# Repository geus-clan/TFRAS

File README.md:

# TFRAS
PCB prototype for sensor board used with resistive automatic ablation sensor.

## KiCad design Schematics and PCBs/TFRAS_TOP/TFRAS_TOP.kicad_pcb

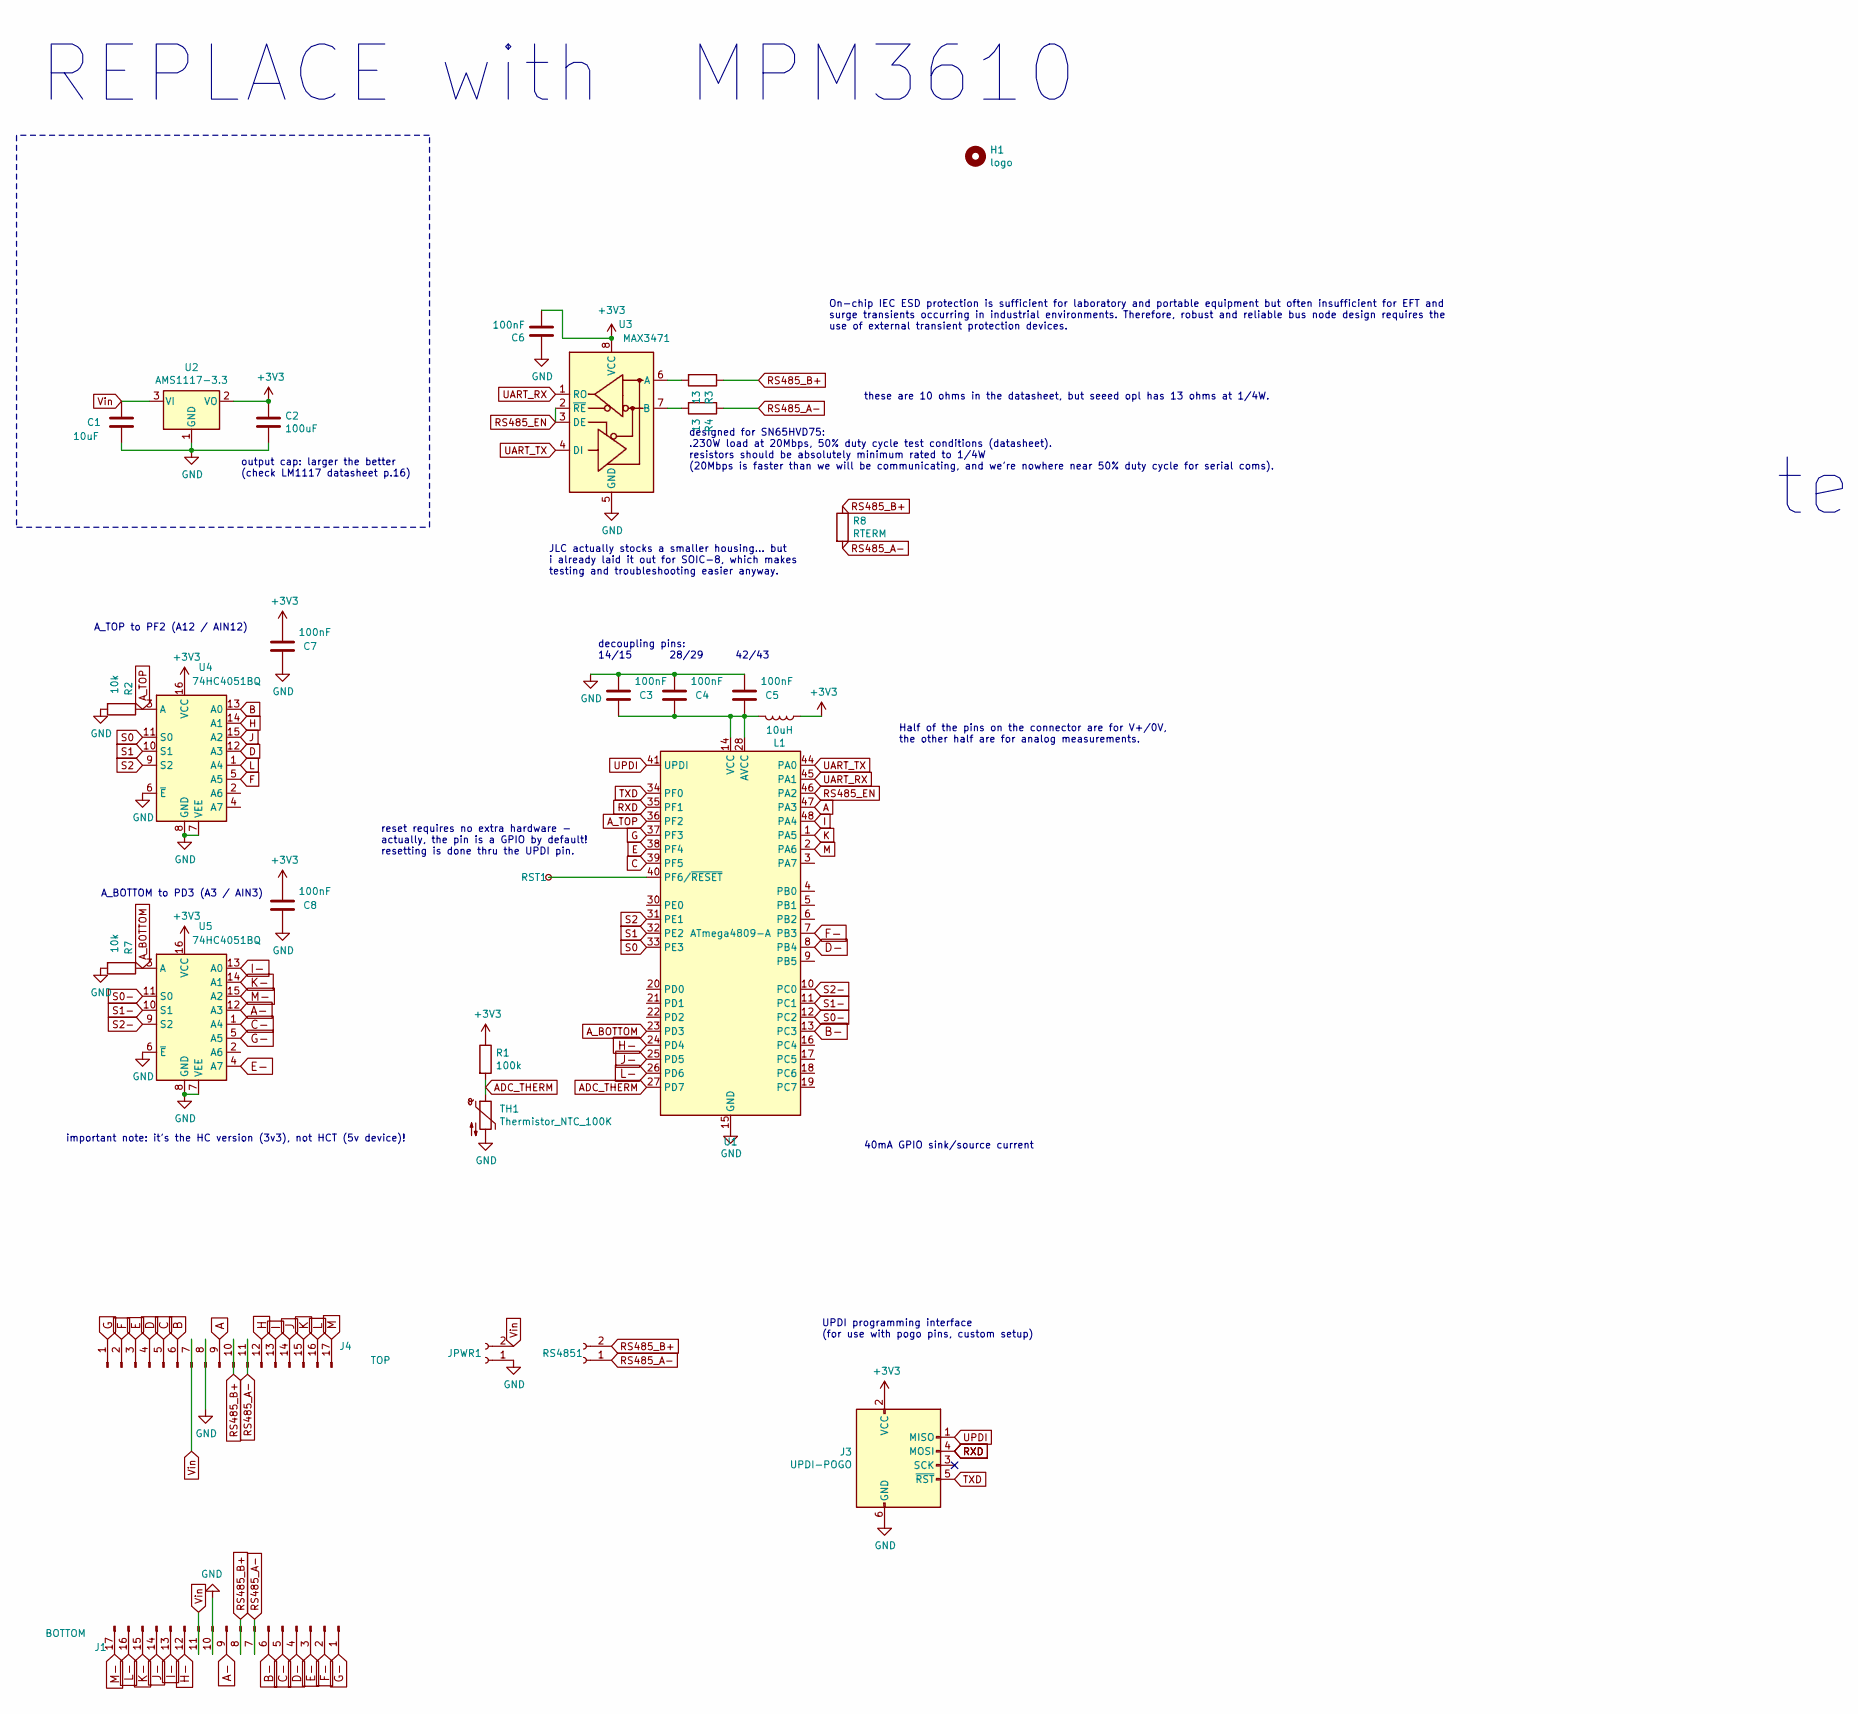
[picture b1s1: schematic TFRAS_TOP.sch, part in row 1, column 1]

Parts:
C1: 10uF; C_1206_3216Metric
C2: 100uF; C_1206_3216Metric
C3, C4, C5, C6, C7, C8: 100nF; C_0402_1005Metric; JLC part number C1525
H1: logo; TFRAS
J1: BOTTOM; Molex_200528-0170_1x17-1MP_P1.00mm_Horizontal
J3: UPDI-POGO; Tag-Connect_TC2030-IDC-NL_2x03_P1.27mm_Vertical; JLC part number ---
J4: TOP; Molex_200528-0170_1x17-1MP_P1.00mm_Horizontal; Mouser part number 538-200528-0170
JPWR1: Conn_01x02_Female; PinHeader_1x02_P1.27mm_Vertical; JLC part number ---
L1: 10uH; L_0603_1608Metric; JLC part number C1035
R1: 100k; R_0402_1005Metric
R2, R7: 10k; R_0805_2012Metric
R3, R4: 13; R_1206_3216Metric; JLC part number C17903
R8: RTERM; R_0805_2012Metric_Pad1.20x1.40mm_HandSolder; JLC part number ---
RS4851: Conn_01x02_Female; PinHeader_1x02_P1.27mm_Vertical; JLC part number ---
RST1: TestPoint_Small; TestPoint_Pad_1.0x1.0mm; JLC part number ---
TH1: Thermistor_NTC_100K; R_0603_1608Metric
U1: ATmega4809-A; TQFP-48_7x7mm_P0.5mm; JLC part number C189475
U2: AMS1117-3.3; SOT-223-3_TabPin2; JLC part number C6186
U3: MAX3471; MSOP-8_3x3mm_P0.65mm
U4, U5: 74HC4051BQ; SOT763-1(DHVQFN16); JLC part number C547696

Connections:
+3V3: C2.1, C6.2, C7.2, C8.2, J3.2 (VCC), L1.1, R1.1, U2.2 (VO), U3.8 (VCC), U4.16 (VCC), U5.16 (VCC)
A: J4.9, U1.47 (PA3)
A-: J1.9, U5.12 (A3)
ADC_THERM: R1.2, TH1.1, U1.27 (PD7)
A_BOTTOM: R7.1, U1.23 (PD3), U5.3 (A)
A_TOP: R2.1, U1.36 (PF2), U4.3 (A)
B: J4.6, U4.13 (A0)
B-: J1.6, U1.13 (PC3)
C: J4.5, U1.39 (PF5)
C-: J1.5, U5.1 (A4)
D: J4.4, U4.12 (A3)
D-: J1.4, U1.8 (PB4)
E: J4.3, U1.38 (PF4)
E-: J1.3, U5.4 (A7)
F: J4.2, U4.5 (A5)
F-: J1.2, U1.7 (PB3)
G: J4.1, U1.37 (PF3)
G-: J1.1, U5.5 (A5)
GND: C1.2, C2.2, C3.2, C4.2, C5.2, C6.1, C7.1, C8.1, J1.10, J3.6 (GND), J4.8, JPWR1.1, R2.2, R7.2, TH1.2, U1.15 (GND), U1.29 (GND), U1.43 (GND), U2.1 (GND), U3.5 (GND), U4.6 (~E), U4.7 (VEE), U4.8 (GND), U5.6 (~E), U5.7 (VEE), U5.8 (GND)
H: J4.12, U4.14 (A1)
H-: J1.12, U1.24 (PD4)
I: J4.13, U1.48 (PA4)
I-: J1.13, U5.13 (A0)
J: J4.14, U4.15 (A2)
J-: J1.14, U1.25 (PD5)
K: J4.15, U1.1 (PA5)
K-: J1.15, U5.14 (A1)
L: J4.16, U4.1 (A4)
L-: J1.16, U1.26 (PD6)
M: J4.17, U1.2 (PA6)
M-: J1.17, U5.15 (A2)
unnamed: C3.1, C4.1, C5.1, L1.2, U1.14 (VCC), U1.28 (AVCC), U1.42 (VCC)
unnamed: R3.2, U3.6 (A)
unnamed: R4.2, U3.7 (B)
unnamed: RST1.1, U1.40 (PF6/~RESET)
RS485_A-: J1.7, J4.11, R4.1, R8.2, RS4851.1
RS485_B+: J1.8, J4.10, R3.1, R8.1, RS4851.2
RS485_EN: U1.46 (PA2), U3.2 (~RE), U3.3 (DE)
RXD: J3.4 (MOSI), U1.35 (PF1)
S0: U1.33 (PE3), U4.11 (S0)
S0-: U1.12 (PC2), U5.11 (S0)
S1: U1.32 (PE2), U4.10 (S1)
S1-: U1.11 (PC1), U5.10 (S1)
S2: U1.31 (PE1), U4.9 (S2)
S2-: U1.10 (PC0), U5.9 (S2)
TXD: J3.5 (~RST), U1.34 (PF0)
UART_RX: U1.45 (PA1), U3.1 (RO)
UART_TX: U1.44 (PA0), U3.4 (DI)
UPDI: J3.1 (MISO), U1.41 (UPDI)
Vin: C1.1, J1.11, J4.7, JPWR1.2, U2.3 (VI)

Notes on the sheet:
test RS485 section
test points from serial port (uart)
40mA GPIO sink/source current
decoupling pins: 14/15 28/29 42/43
UPDI programming interface (for use with pogo pins, custom setup)
A_TOP to PF2 (A12 / AIN12)
A_BOTTOM to PD3 (A3 / AIN3)
Half of the pins on the connector are for V+/0V, the other half are for analog measurements.
On-chip IEC ESD protection is sufficient for laboratory and portable equipment but often insufficient for EFT and surge transients occurring in industrial environments. Therefore, robust and reliable bus node design requires the use of external transient protection devices.
output cap: larger the better (check LM1117 datasheet p.16)
designed for SN65HVD75: .230W load at 20Mbps, 50% duty cycle test conditions (datasheet). resistors should be absolutely minimum rated to 1/4W (20Mbps is faster than we will be communicating, and we’re nowhere near 50% duty cycle for serial coms).
JLC actually stocks a smaller housing… but i already laid it out for SOIC-8, which makes testing and troubleshooting easier anyway.
these are 10 ohms in the datasheet, but seeed opl has 13 ohms at 1/4W.
reset requires no extra hardware - actually, the pin is a GPIO by default! resetting is done thru the UPDI pin.
important note: it’s the HC version (3v3), not HCT (5v device)!
REPLACE with MPM3610

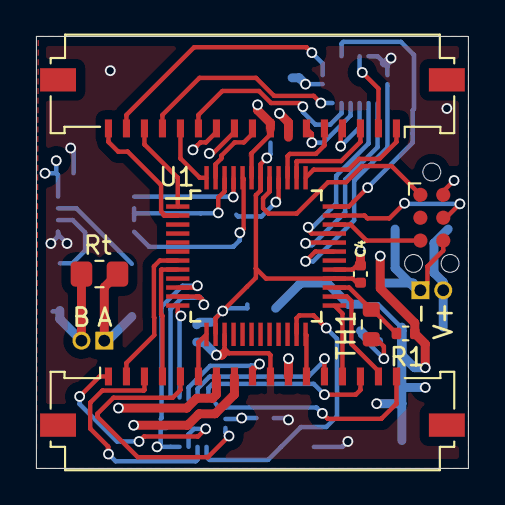
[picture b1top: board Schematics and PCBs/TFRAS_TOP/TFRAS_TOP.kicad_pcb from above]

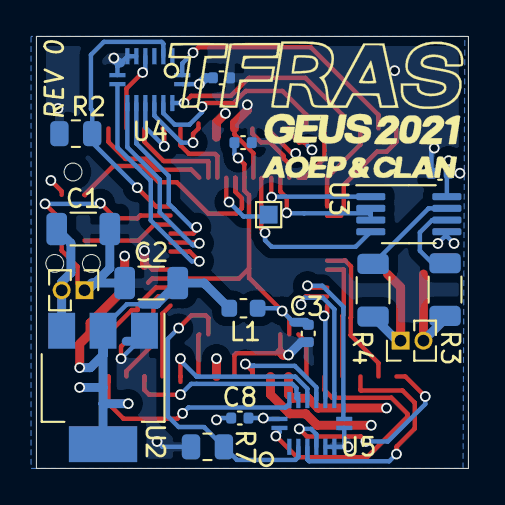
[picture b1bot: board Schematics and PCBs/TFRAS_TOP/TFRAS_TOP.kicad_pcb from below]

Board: 4 copper layers, 24.0 x 24.0 mm, 28 parts (20 on the bottom side), 50 nets.

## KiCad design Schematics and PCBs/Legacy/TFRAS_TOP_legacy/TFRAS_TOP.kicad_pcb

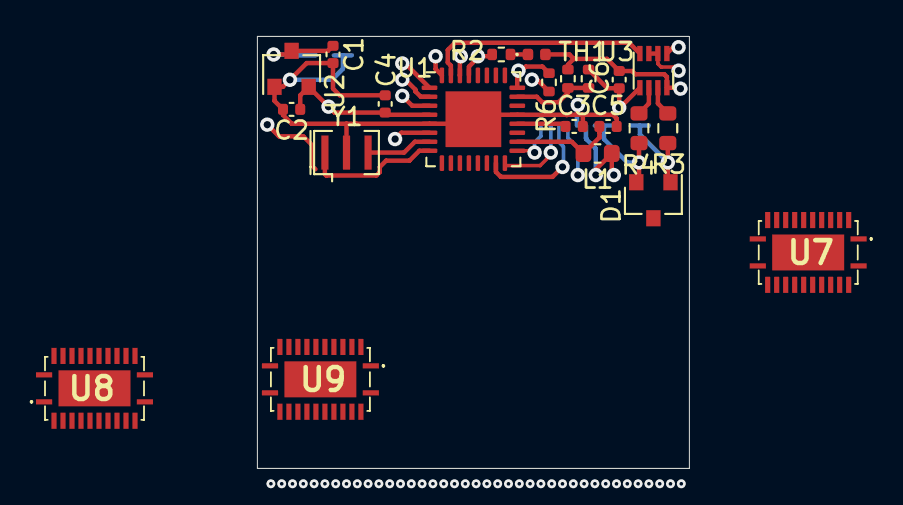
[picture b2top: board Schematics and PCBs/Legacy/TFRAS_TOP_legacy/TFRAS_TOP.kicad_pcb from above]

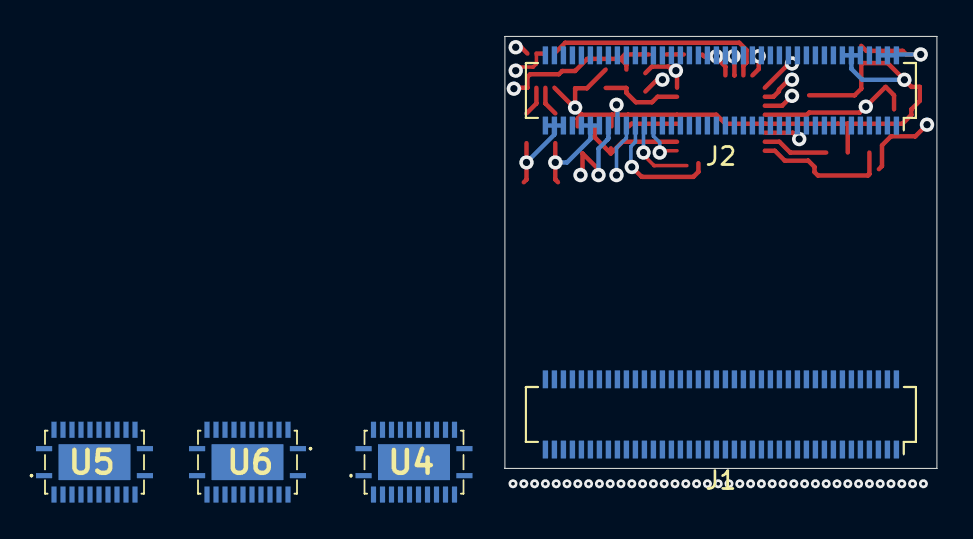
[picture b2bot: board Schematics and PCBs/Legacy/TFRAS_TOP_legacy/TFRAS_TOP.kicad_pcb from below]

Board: 4 copper layers, 24.0 x 24.0 mm, 27 parts (5 on the bottom side), 80 nets.

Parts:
C1: 1uF/16V; C_0402_1005Metric
C2: 1uF/6.3V; C_0402_1005Metric
C3, C4, C5, C6: 100nF; C_0402_1005Metric
D1: CDSOT23-SM712; SOT-23
D2: 1N4148; D_0402_1005Metric
J1, J2: Molex 555600807; Molex_SlimStack_55560-0801_2x40_P0.50mm_Vertical
L1: 10uH; L_0603_1608Metric
R1, R2, R6: 10K; R_0402_1005Metric
R3, R4: 10; R_0603_1608Metric
TH1: Thermistor_NTC_10K; R_0402_1005Metric
U1: ATmega328PB-MU; QFN-32-1EP_5x5mm_P0.5mm_EP3.1x3.1mm
U2: MCP1754S-3302xCB; SOT-23
U3: MAX14783EATA+T; DFN-8_2x2mm_P0.5mm
U4, U5, U6, U7, U8, U9: 74HC4067BQ,118; 74LVCH8T245BQQ10J
Y1: Resonator; Resonator_SMD_muRata_CSTxExxV-3Pin_3.0x1.1mm

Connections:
+3V3: C2.1, C4.1, C6.2, D2.2, J2.65, L1.1, R1.1, U1.4, U2.2, U3.8, U4.1, U4.24, U5.1, U5.24, U6.1, U6.24, U7.24, U8.24, U9.24
ADC: R1.2, TH1.1, U1.23
BS0: J1.39, J1.41
BS1: J1.37, U7.9
BS2: J1.28, U7.8
BS3: J1.35, U7.7
BS4: J1.33, U7.6
BS5: J1.24, U7.5
BS6: J1.29, U7.4
BS7: J1.20, U7.3
BS8: J1.19, U4.23, U7.2
BS9: J1.16, U4.2, U4.22, U7.23
BS10: J1.14, U4.3, U4.21, U7.22
BS11: J1.12, U4.4, U4.20, U7.21
BS12: J1.10, U4.5, U4.19, U7.20
BS13: J1.8, U4.6, U4.18, U7.19
BS14: J1.6, U4.7, U4.17, U7.18
BS15: J1.3, U4.16, U7.17
BS16: J1.4, U4.8, U5.9, U7.16
BS17: J1.1, U5.8, U8.9
BS18: J1.2, U4.9, U5.7, U8.8
BS19: J1.43, U5.6, U8.7
BS20: J1.54, U5.5, U8.6
BS21: J1.45, U5.4, U8.5
BS22: J1.47, U5.3, U8.4
BS23: J1.58, U5.2, U8.3
BS24: J1.51, U5.23, U8.2
BS25: J1.62, U5.22, U8.23
BS26: J1.61, U5.21, U8.22
BS27: J1.66, U5.20, U8.21
BS28: J1.68, U5.19, U8.20
BS29: J1.70, U5.18, U8.19
BS30: J1.72, U5.17, U8.18
BS31: J1.74, U5.16, U8.17
BS32: J1.76, U6.9, U8.16
BS33: J1.77, U6.8, U9.9
BS34: J1.78, U6.7, U9.8
BS35: J1.79, U6.6, U9.7
BS36: J1.80, U6.5, U9.6
BS37: J1.42, U6.4, U9.5
BS38: J1.40, U6.3, U9.4
BS39: J1.36, U6.2, U9.3
BS40: J1.32, U6.23, U9.2
BS41: J1.26, U6.22, U9.23
BS42: J1.22, U6.21, U9.22
BS43: J1.18, U6.20, U9.21
BS44: J1.46, U6.19, U9.20
BS45: J1.50, U6.18, U9.19
BS46: J1.56, U6.17, U9.18
BS47: J1.60, U6.16, U9.17
BS48: J1.64, U9.16
E1: U1.9, U4.15
E2: U1.10, U7.15
E3: U1.11, U5.15
E4: U1.12, U8.15
E5: U1.13, U6.15
E6: U1.14, U9.15
GND: C1.2, C2.2, C3.2, C4.2, C5.2, C6.1, D1.3, J1.13, J1.15, J1.17, J2.10, J2.12, J2.14, J2.63, R6.1, TH1.2, U1.5, U1.21, U1.33, U2.1, U3.5, U4.12, U5.12, U6.12, U7.12, U8.12, U9.12, Y1.2
MISO: J2.57, U1.16
MOSI: J2.59, U1.15
unnamed: C3.1, U1.20
unnamed: C5.1, L1.2, U1.18
unnamed: D2.1, R2.1
unnamed: R3.2, U3.7
unnamed: R4.2, U3.6
unnamed: U1.7, Y1.3
unnamed: U1.8, Y1.1
RS485_A-: D1.2, J1.71, J1.73, J1.75, J2.67, J2.69, J2.71, R4.1
RS485_B+: D1.1, J1.63, J1.65, J1.67, J2.75, J2.77, J2.79, R3.1
RS485_EN: U1.32, U3.2, U3.3
RST: J2.61, R2.2, U1.29
S0: U1.1, U4.10, U5.10, U6.10, U7.10, U8.10, U9.10
S1: U1.2, U4.11, U5.11, U6.11, U7.11, U8.11, U9.11
S2: U1.3, U4.14, U5.14, U6.14, U7.14, U8.14, U9.14
S3: U1.6, U4.13, U5.13, U6.13, U7.13, U8.13, U9.13
SCK: J2.55, U1.17
UART_RX: U1.30, U3.1
UART_TX: U1.31, U3.4
Vin: C1.1, J1.5, J1.7, J1.9, J2.2, J2.4, J2.6, U2.3
Z: R6.2, U1.24, U7.1, U8.1, U9.1

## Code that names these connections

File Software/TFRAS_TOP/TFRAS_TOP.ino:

//to do:
//  address individual boards
//  wait to transmit
//  read center of flex pcb

#define UART_TX 44
#define UART_RX 45
#define RS485_EN 46

#define S0 33
#define S1 32
#define S2 31

#define S0- 12
#define S1- 11
#define S2- 10

#define A_TOP 36
#define A_BOTTOM 23
#define ADC_THERM 27

#define A 47
#define C 39
#define E 38
#define G 37
#define I 48
#define K 1
#define M 2

#define B_ 13
#define D_ 8
#define F_ 7
#define H_ 24
#define J_ 25
#define L_ 26


uint16_t topFlex[11];     //arrays for storing the cm of readings. e.g. topFlex[6] is between 6 and 7cm
uint16_t bottomFlex[11];

void setup() {
Serial.begin(9600);

  for(int i=1;i<49;i++){  //set most GPIOs as inputs (high impedence, e.g. open circuit)
    if(i==28){i=34;}
    if(i==40){i=47;}
    pinMode(i, INPUT);
  }
  
  for(int i=10;i<34;i++){  //set address pins as outputs
    if(i==13){i=31;}
    pinMode(i, OUTPUT);
  }

  pinMode(RS485_EN, OUTPUT);
  
}



void muxRead(){
  digitalWrite(S0, LOW); //address A0
  digitalWrite(S1, LOW);    //top connector: B
  digitalWrite(S2, LOW);    //bottom connector: I_

  topFlex[0]= readFlex(A, A_TOP); //power pin, mux pin
  topFlex[1]= readFlex(C, A_TOP);

  bottomFlex[7]= readFlex(H_, A_BOTTOM);
  bottomFlex[8]= readFlex(J_, A_BOTTOM);
  
  digitalWrite(S0, HIGH); //address A1
  digitalWrite(S1, LOW);    //top connector: H
  digitalWrite(S2, LOW);    //bottom connector: K_

  topFlex[6]= readFlex(G, A_TOP);
  topFlex[7]= readFlex(I, A_TOP);

  bottomFlex[9]= readFlex(J_, A_BOTTOM);
  bottomFlex[10]= readFlex(L_, A_BOTTOM);

  digitalWrite(S0, LOW); //address A2
  digitalWrite(S1, HIGH);   //top connector: J
  digitalWrite(S2, LOW);    //bottom connector: M_

  topFlex[8]= readFlex(I, A_TOP);
  topFlex[9]= readFlex(K, A_TOP);

  bottomFlex[11]= readFlex(L_, A_BOTTOM);

  digitalWrite(S0, HIGH); //address A3
  digitalWrite(S1, HIGH);   //top connector:D
  digitalWrite(S2, LOW);    //bottom connector: A-

  topFlex[2]= readFlex(C, A_TOP);
  topFlex[3]= readFlex(E, A_TOP);

  bottomFlex[0]= readFlex(B_, A_BOTTOM);
  
  digitalWrite(S0, LOW); //address A4
  digitalWrite(S1, LOW);    //top connector: L
  digitalWrite(S2, HIGH);   //bottom connector: C_

  topFlex[10]= readFlex(K, A_TOP);
  topFlex[11]= readFlex(M, A_TOP);
  
  bottomFlex[1]= readFlex(B_, A_BOTTOM);
  bottomFlex[2]= readFlex(D_, A_BOTTOM);

  digitalWrite(S0, HIGH); //address A5
  digitalWrite(S1, LOW);    //top connector: F
  digitalWrite(S2, HIGH);   //bottom connector: G_

  topFlex[4]= readFlex(E, A_TOP);
  topFlex[5]= readFlex(G, A_TOP);

  bottomFlex[5]= readFlex(F_, A_BOTTOM);
  bottomFlex[6]= readFlex(H_, A_BOTTOM);

  digitalWrite(S0, LOW); //address A6
  digitalWrite(S1, HIGH);   
  digitalWrite(S2, HIGH);   //bottom connector: E_

  bottomFlex[3]= readFlex(D_, A_BOTTOM);
  bottomFlex[4]= readFlex(F_, A_BOTTOM);
}




uint16_t readFlex(int powerPin, int readPin){ //readPin is just the mux output pin
  
//set A as output
//apply power to A
//read B
//remove power to A and reset to high-Z input
  
  pinMode(powerPin, OUTPUT);
  digitalWrite(powerPin, HIGH);
  uint16_t result = analogRead(readPin);
  pinMode(powerPin, INPUT);
  return result;
}


void printResults(){
  digitalWrite(RS485_EN, HIGH);
  for(int i=0;i<12;i++){
    Serial.print(topFlex[i]);
    Serial.print(", ");
  }
  Serial.println();
}



void loop() {
  muxRead();
  printResults();
  delay(1000);
}

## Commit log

2021-10-21 organization and updating project files
2021-10-21 Organization
2021-10-21 cleaned
2021-10-22 PCB finished with seeed BOM
2021-10-26 added pdf schematic
2022-01-05 tfras pcb
2022-01-21 Create TFRAS_singleread.ino
    in-progress software
2022-07-06 tfras software upodates
2022-08-12 software
2022-08-16 software updates
2022-08-17 functional prototype software
2022-08-17 bug fix
2022-08-18 functional firehose prototpe
2022-08-24 preparing for field
2022-08-24 field ready
2022-12-15 add PDFs
2024-07-09 2024
    claude helped
